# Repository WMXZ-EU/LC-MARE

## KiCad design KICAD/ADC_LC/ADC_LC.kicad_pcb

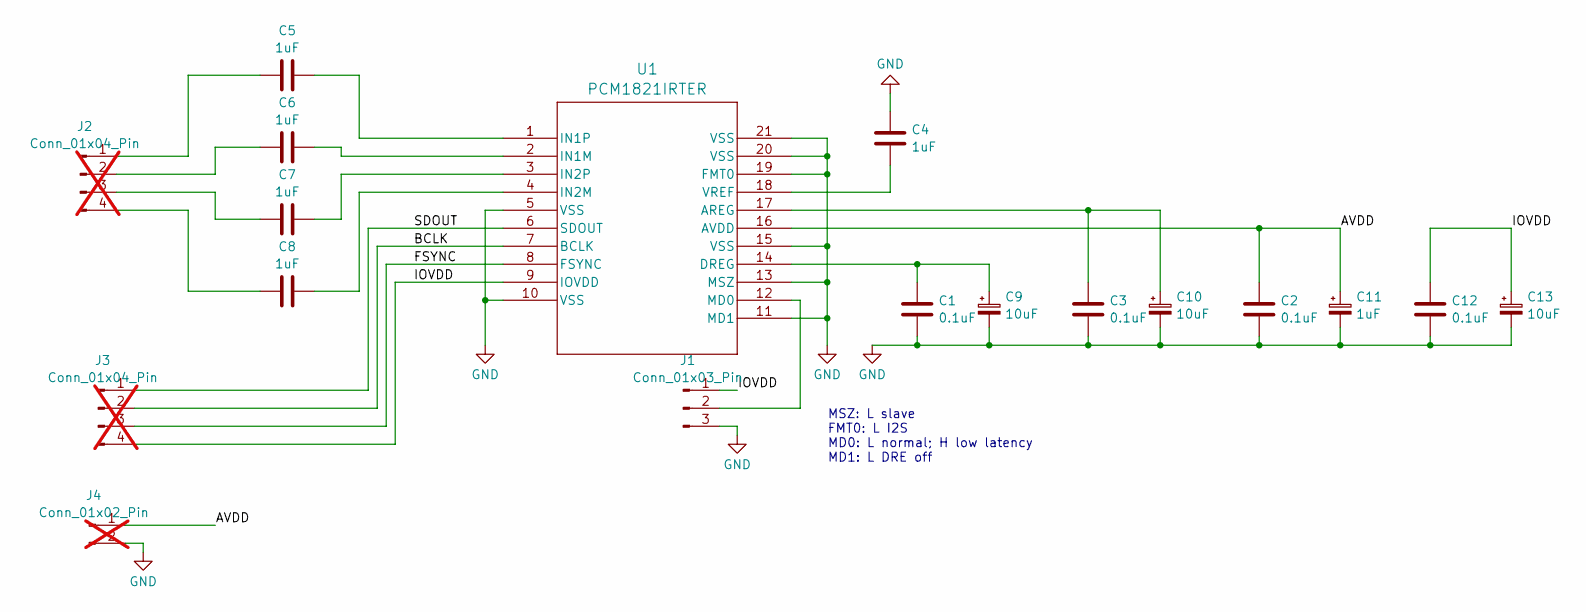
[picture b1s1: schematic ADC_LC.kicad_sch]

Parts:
C1, C2, C3, C12: 0.1uF; C_0402_1005Metric
C4, C5, C6, C7, C8: 1uF; C_0402_1005Metric
C9, C10, C13: 10uF; C_0805_2012Metric
C11: 1uF; C_0805_2012Metric
J1: Conn_01x03_Pin; SolderJumper-3_P1.3mm_Open_Pad1.0x1.5mm
J2, J3: Conn_01x04_Pin; PinHeader_1x04_P2.54mm_Vertical; not fitted
J4: Conn_01x02_Pin; PinHeader_1x02_P2.54mm_Vertical; not fitted
U1: PCM1821IRTER; QFN_820IRTER_TEX

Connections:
/AVDD: C2.1, C11.1, J4.1, U1.16 (AVDD)
/BCLK: J3.2, U1.7 (BCLK)
/FSYNC: J3.3, U1.8 (FSYNC)
/IOVDD: C12.1, C13.1, J1.1, J3.4, U1.9 (IOVDD)
/SDOUT: J3.1, U1.6 (SDOUT)
GND: C1.2, C2.2, C3.2, C4.1, C9.2, C10.2, C11.2, C12.2, C13.2, J1.3, J4.2, U1.5 (VSS), U1.10 (VSS), U1.11 (MD1), U1.13 (MSZ), U1.15 (VSS), U1.19 (FMT0), U1.20 (VSS), U1.21 (VSS)
unnamed: J1.2, U1.12 (MD0)
unnamed: C5.1, J2.1
unnamed: C6.1, J2.2
unnamed: C7.1, J2.3
unnamed: C8.1, J2.4
unnamed: C3.1, C10.1, U1.17 (AREG)
unnamed: C1.1, C9.1, U1.14 (DREG)
unnamed: C6.2, U1.2 (IN1M)
unnamed: C5.2, U1.1 (IN1P)
unnamed: C8.2, U1.4 (IN2M)
unnamed: C7.2, U1.3 (IN2P)
unnamed: C4.2, U1.18 (VREF)

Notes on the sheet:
MSZ: L slave FMT0: L I2S MD0: L normal; H low latency MD1: L DRE off

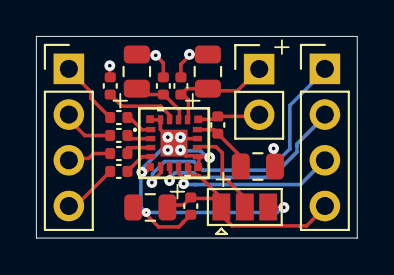
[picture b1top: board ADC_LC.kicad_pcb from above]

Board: 2 copper layers, 17.8 x 11.2 mm, 18 parts (0 on the bottom side), 18 nets.

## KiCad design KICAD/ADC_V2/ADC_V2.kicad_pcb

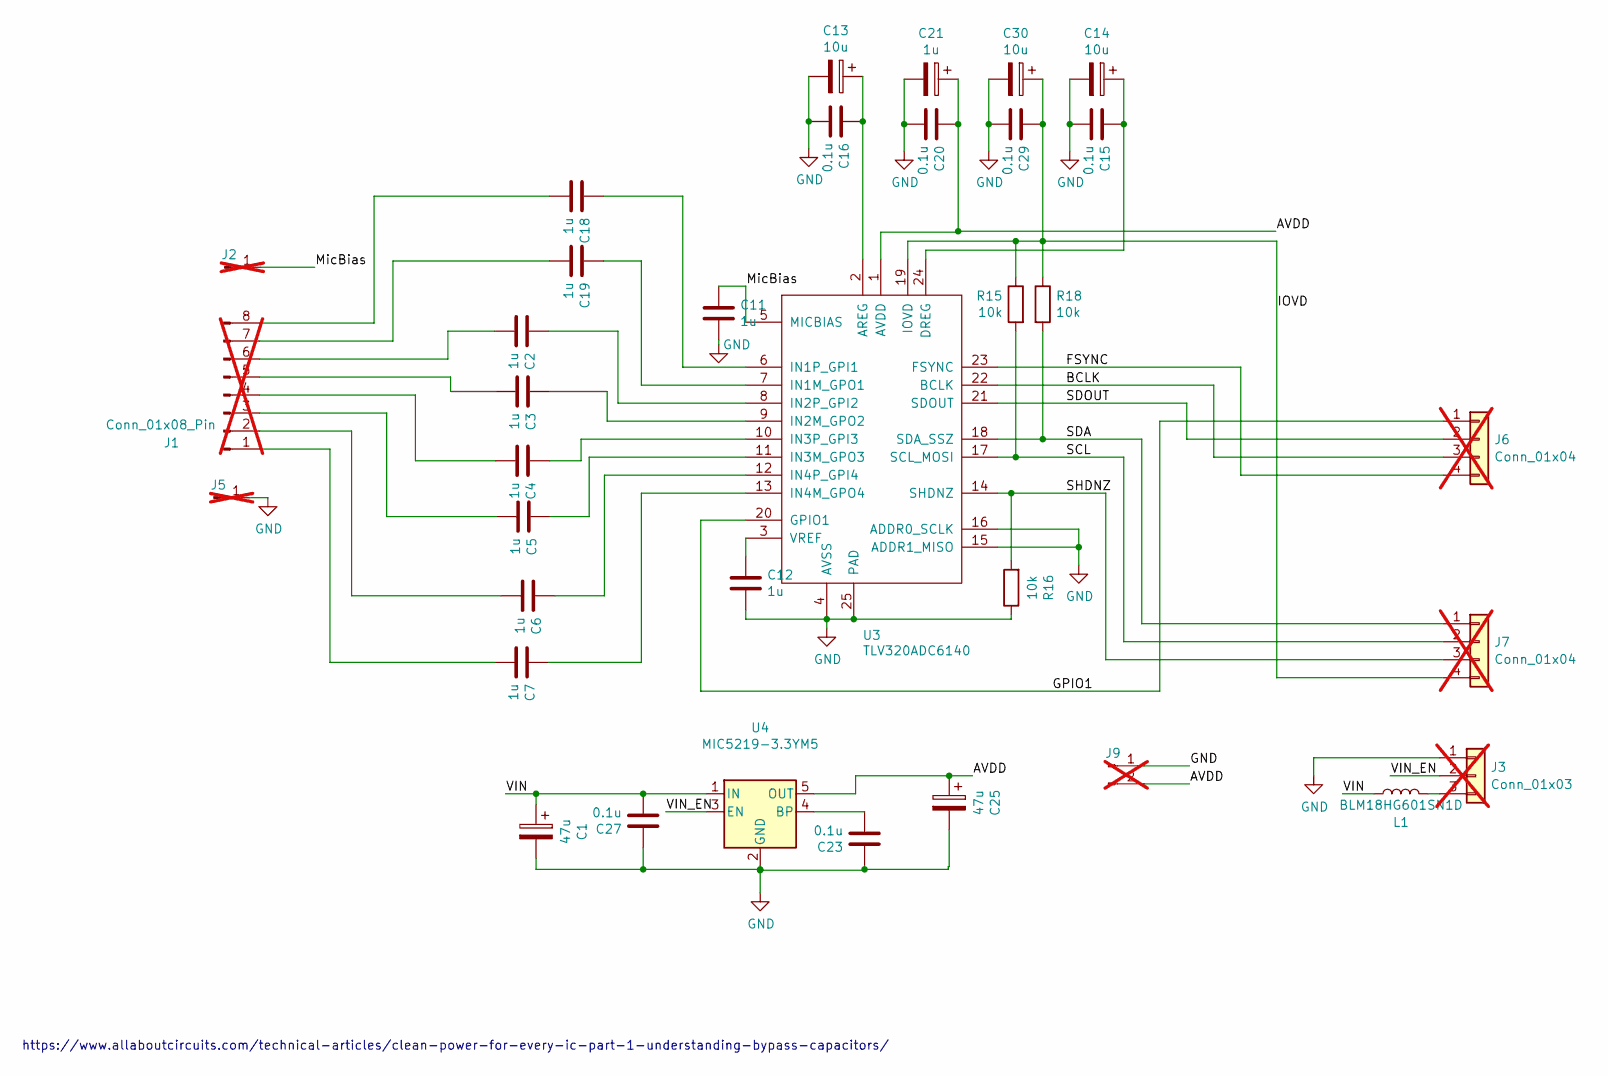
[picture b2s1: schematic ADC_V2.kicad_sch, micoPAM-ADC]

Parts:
C1, C25: 47u; CP_EIA-3216-12_Kemet-S
C2, C3, C4, C5, C6, C7, C11, C12, C18, C19: 1u; C_0603_1608Metric
C13, C14, C30: 10u; CP_EIA-2012-15_AVX-P
C15, C16, C20, C23, C27, C29: 0.1u; C_0603_1608Metric
C21: 1u; CP_EIA-2012-15_AVX-P
J1: Conn_01x08_Pin; PinHeader_1x08_P1.27mm_Vertical; not fitted
J2, J5: Conn_01x01_Pin; PinHeader_1x01_P2.54mm_Vertical; not fitted
J3: Conn_01x03; PinHeader_1x03_P1.27mm_Vertical; not fitted
J6, J7: Conn_01x04; PinHeader_1x04_P1.27mm_Vertical; not fitted
J9: Conn_01x02_Pin; PinHeader_1x02_P1.27mm_Vertical; not fitted
L1: BLM18HG601SN1D; L_0603_1608Metric
R15, R16, R18: 10k; R_0603_1608Metric
U3: TLV320ADC6140; QFN-24-1EP_4x4mm_P0.5mm_EP2.7x2.7mm_ThermalVias
U4: MIC5219-3.3YM5; SOT-23-5

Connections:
/AVDD: C20.1, C21.1, C25.1, J9.2, U3.1 (AVDD), U4.5 (OUT)
/BCLK: J6.3, U3.22 (BCLK)
/FSYNC: J6.4, U3.23 (FSYNC)
/GPIO1: J6.1, U3.20 (GPIO1)
/IOVD: C29.1, C30.1, J7.4, R15.1, R18.1, U3.19 (IOVD)
/MicBias: C11.1, J2.1, U3.5 (MICBIAS)
/SCL: J7.2, R15.2, U3.17 (SCL_MOSI)
/SDA: J7.1, R18.2, U3.18 (SDA_SSZ)
/SDOUT: J6.2, U3.21 (SDOUT)
/SHDNZ: J7.3, R16.2, U3.14 (SHDNZ)
/VIN: C1.1, C27.2, L1.1, U4.1 (IN)
/VIN_EN: J3.2, U4.3 (EN)
GND: C1.2, C11.2, C12.2, C13.2, C14.2, C15.2, C16.2, C20.2, C21.2, C23.1, C25.2, C27.1, C29.2, C30.2, J3.1, J5.1, J9.1, R16.1, U3.4 (AVSS), U3.15 (ADDR1_MISO), U3.16 (ADDR0_SCLK), U3.25 (PAD), U4.2 (GND)
unnamed: C7.2, J1.1
unnamed: C6.2, J1.2
unnamed: C5.2, J1.3
unnamed: C4.2, J1.4
unnamed: C3.2, J1.5
unnamed: C2.2, J1.6
unnamed: C19.2, J1.7
unnamed: C18.2, J1.8
unnamed: J3.3, L1.2
unnamed: C13.1, C16.1, U3.2 (AREG)
unnamed: C14.1, C15.1, U3.24 (DREG)
unnamed: C19.1, U3.7 (IN1M_GPO1)
unnamed: C18.1, U3.6 (IN1P_GPI1)
unnamed: C3.1, U3.9 (IN2M_GPO2)
unnamed: C2.1, U3.8 (IN2P_GPI2)
unnamed: C5.1, U3.11 (IN3M_GPO3)
unnamed: C4.1, U3.10 (IN3P_GPI3)
unnamed: C7.1, U3.13 (IN4M_GPO4)
unnamed: C6.1, U3.12 (IN4P_GPI4)
unnamed: C12.1, U3.3 (VREF)
unnamed: C23.2, U4.4 (BP)

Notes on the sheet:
https://www.allaboutcircuits.com/technical-articles/clean-power-for-every-ic-part-1-understanding-bypass-capacitors/

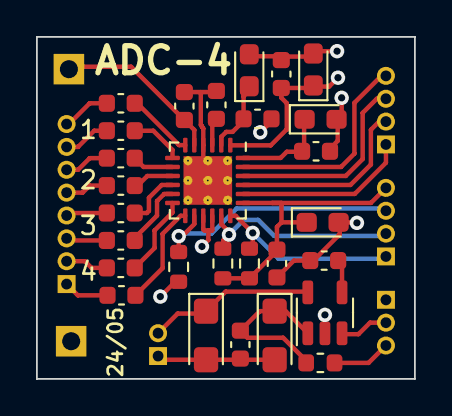
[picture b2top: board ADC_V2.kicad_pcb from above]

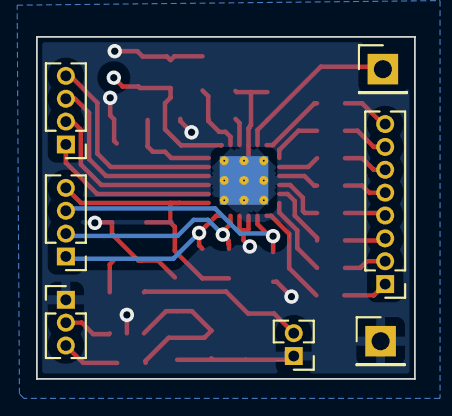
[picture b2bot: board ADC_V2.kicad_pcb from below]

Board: 4 copper layers, 21.0 x 19.0 mm, 35 parts (7 on the bottom side), 34 nets.

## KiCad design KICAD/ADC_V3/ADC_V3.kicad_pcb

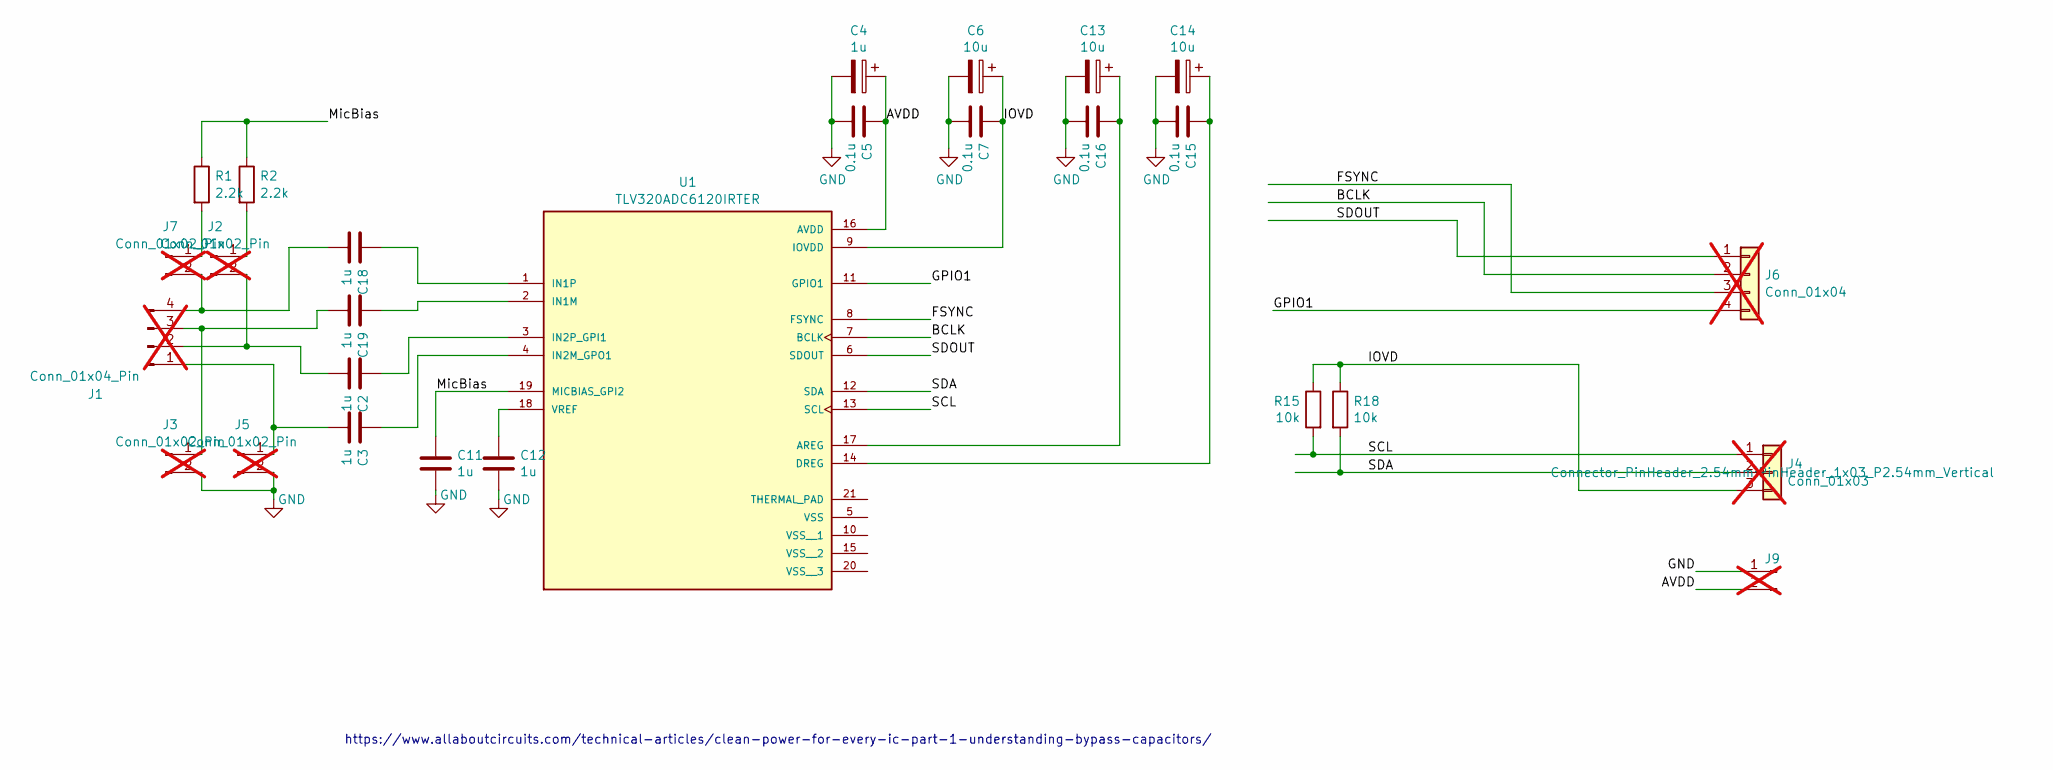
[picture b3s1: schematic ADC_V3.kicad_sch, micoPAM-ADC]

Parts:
C2, C3, C11, C12, C18, C19: 1u; C_0603_1608Metric
C4: 1u; CP_EIA-2012-15_AVX-P
C5, C7, C15, C16: 0.1u; C_0603_1608Metric
C6, C13, C14: 10u; CP_EIA-2012-15_AVX-P
J1: Conn_01x04_Pin; PinHeader_1x04_P2.54mm_Vertical; not fitted
J2, J3, J5, J7: Conn_01x02_Pin; PinHeader_1x02_P1.00mm_Vertical; not fitted
J4: Conn_01x03; PinHeader_1x03_P2.54mm_Vertical; not fitted
J6: Conn_01x04; PinHeader_1x04_P2.54mm_Vertical; not fitted
J9: Conn_01x02_Pin; PinHeader_1x02_P2.54mm_Vertical; not fitted
R1, R2: 2.2k; R_0402_1005Metric
R15, R18: 10k; R_0603_1608Metric
U1: TLV320ADC6120IRTER; IC_TLV320ADC6120IRTER; PARTREV A

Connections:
/AVDD: C4.1, C5.1, J9.2, U1.16 (AVDD)
/BCLK: J6.2, U1.7 (BCLK)
/FSYNC: J6.3, U1.8 (FSYNC)
/GPIO1: J6.4, U1.11 (GPIO1)
/IOVD: C6.1, C7.1, J4.3, R15.1, R18.1, U1.9 (IOVDD)
/MicBias: C11.1, R1.1, R2.1, U1.19 (MICBIAS_GPI2)
/SCL: J4.1, R15.2, U1.13 (SCL)
/SDA: J4.2, R18.2, U1.12 (SDA)
/SDOUT: J6.1, U1.6 (SDOUT)
GND: C4.2, C5.2, C6.2, C7.2, C11.2, C12.2, C13.2, C14.2, C15.2, C16.2, J3.2, J5.2, J9.1, U1.5 (VSS), U1.10 (VSS__1), U1.15 (VSS__2), U1.20 (VSS__3), U1.21 (THERMAL_PAD), U1.22, U1.23, U1.24, U1.25
unnamed: C3.2, J1.1, J5.1
unnamed: C2.2, J1.2, J2.2
unnamed: C19.2, J1.3, J3.1
unnamed: C18.2, J1.4, J7.2
unnamed: J2.1, R2.2
unnamed: J7.1, R1.2
unnamed: C13.1, C16.1, U1.17 (AREG)
unnamed: C14.1, C15.1, U1.14 (DREG)
unnamed: C19.1, U1.2 (IN1M)
unnamed: C18.1, U1.1 (IN1P)
unnamed: C3.1, U1.4 (IN2M_GPO1)
unnamed: C2.1, U1.3 (IN2P_GPI1)
unnamed: C12.1, U1.18 (VREF)

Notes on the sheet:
https://www.allaboutcircuits.com/technical-articles/clean-power-for-every-ic-part-1-understanding-bypass-capacitors/

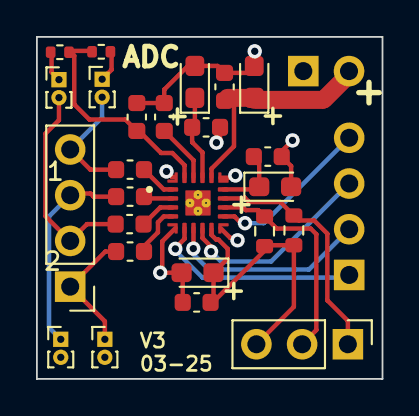
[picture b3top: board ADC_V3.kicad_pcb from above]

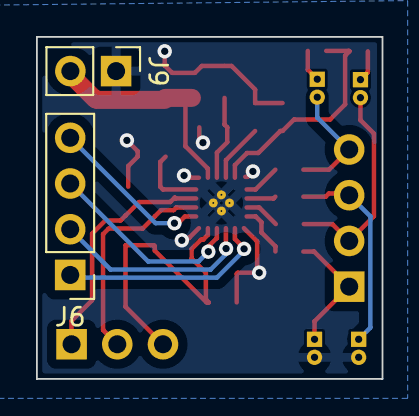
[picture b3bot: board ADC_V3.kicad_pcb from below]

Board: 2 copper layers, 19.2 x 19.0 mm, 27 parts (2 on the bottom side), 23 nets.

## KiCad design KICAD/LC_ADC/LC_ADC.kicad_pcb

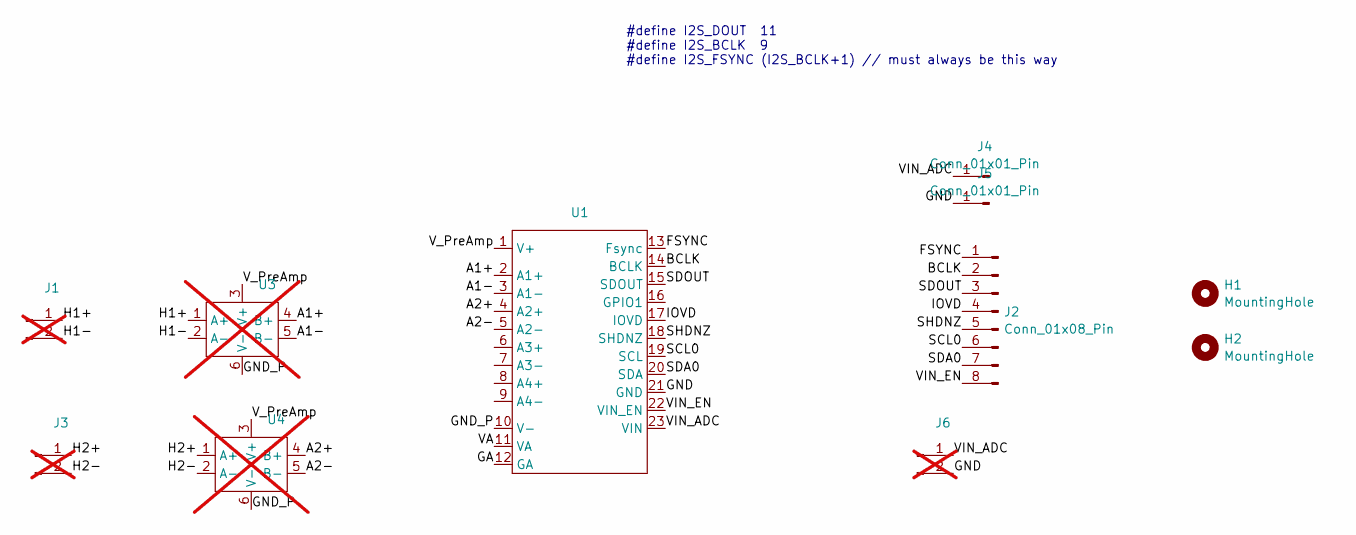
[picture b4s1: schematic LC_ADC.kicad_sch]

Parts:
H1, H2: MountingHole; MountingHole_3.2mm_M3
J1, J3: Conn_01x02_Male; Molex_PicoBlade_53048-0210_1x02_P1.25mm_Horizontal; not fitted
J2: Conn_01x08_Pin; PinHeader_1x08_P2.54mm_Vertical
J4, J5: Conn_01x01_Pin; PinHeader_1x01_P2.54mm_Vertical
J6: Conn_01x02_Male; PinHeader_1x02_P1.27mm_Vertical; not fitted
U1: ADC_V2
U3, U4: preAmp2; not fitted

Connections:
/A1+: U1.2 (A1+), U3.4 (B+)
/A1-: U1.3 (A1-), U3.5 (B-)
/A2+: U1.4 (A2+), U4.4 (B+)
/A2-: U1.5 (A2-), U4.5 (B-)
/BCLK: J2.2, U1.14 (BCLK)
/FSYNC: J2.1, U1.13 (Fsync)
/GA: U1.12 (GA)
/GND: J5.1, J6.2, U1.21 (GND)
/GND_P: U1.10 (V-), U3.6 (V-), U4.6 (V-)
/H1+: J1.1, U3.1 (A+)
/H1-: J1.2, U3.2 (A-)
/H2+: J3.1, U4.1 (A+)
/H2-: J3.2, U4.2 (A-)
/IOVD: J2.4, U1.17 (IOVD)
/SCL0: J2.6, U1.19 (SCL)
/SDA0: J2.7, U1.20 (SDA)
/SDOUT: J2.3, U1.15 (SDOUT)
/SHDNZ: J2.5, U1.18 (SHDNZ)
/VA: U1.11 (VA)
/VIN_ADC: J4.1, J6.1, U1.23 (VIN)
/VIN_EN: J2.8, U1.22 (VIN_EN)
/V_PreAmp: U1.1 (V+), U3.3 (V+), U4.3 (V+)

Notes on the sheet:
#define I2S_DOUT 11 #define I2S_BCLK 9 #define I2S_FSYNC (I2S_BCLK+1) // must always be this way

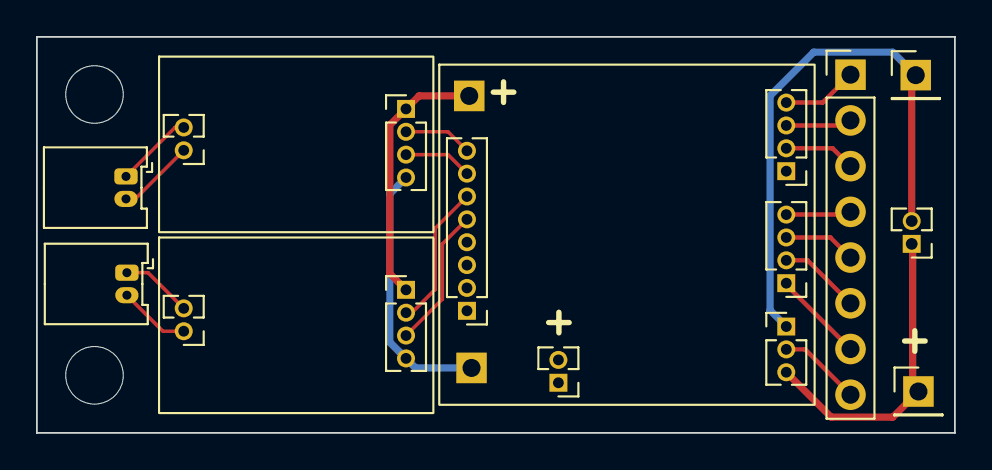
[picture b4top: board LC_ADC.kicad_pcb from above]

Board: 2 copper layers, 51.0 x 22.0 mm, 12 parts (0 on the bottom side), 20 nets.

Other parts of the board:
J10: rtc; rtc2

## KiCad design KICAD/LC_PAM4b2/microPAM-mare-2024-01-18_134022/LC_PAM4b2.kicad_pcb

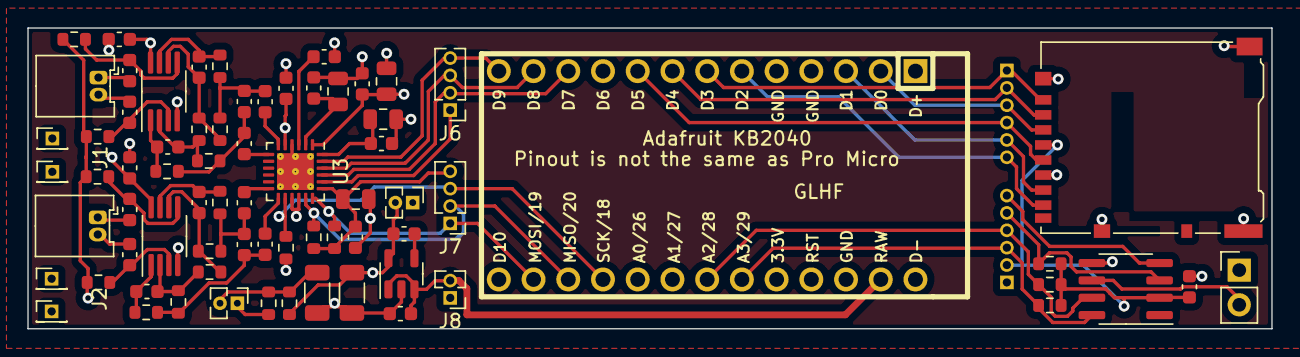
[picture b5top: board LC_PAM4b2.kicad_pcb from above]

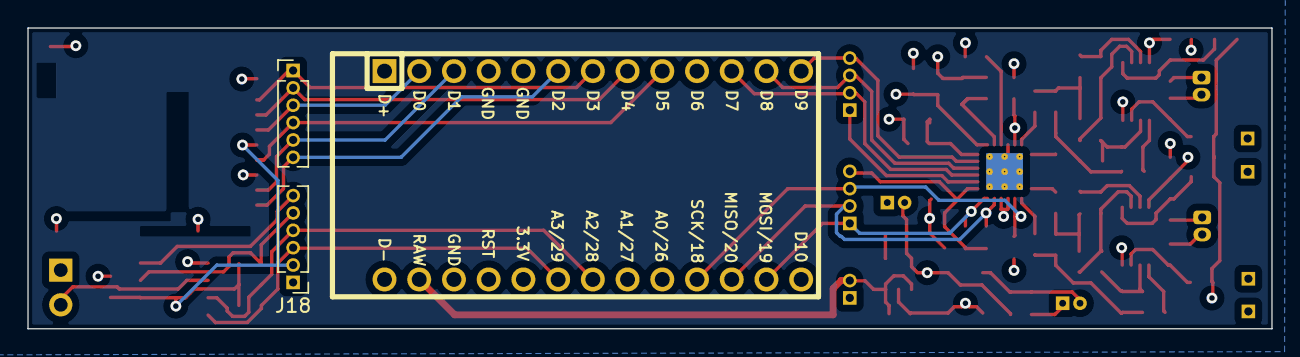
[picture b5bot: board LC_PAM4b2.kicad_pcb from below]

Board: 4 copper layers, 91.0 x 22.0 mm, 74 parts (2 on the bottom side), 52 nets.

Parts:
C1, C2, C7, C8, C11, C12, C18, C19, C24, C28: 1u; C_0603_1608Metric
C3, C4, C9, C10: 15p; C_0603_1608Metric
C5, C6, C15, C16, C20, C23, C27, C29, C101: 0.1u; C_0603_1608Metric
C13, C14, C30: 10u; C_0805_2012Metric
C17, C22: 2700p; C_0603_1608Metric
C21: 1u; C_0805_2012Metric
C25, C26: 47u; C_1206_3216Metric
J1, J2: Conn_01x02_Male; Molex_PicoBlade_53048-0210_1x02_P1.25mm_Horizontal
J3, J4, J5, J11: Conn_01x01_Pin; PinHeader_1x01_P1.27mm_Vertical
J6, J7: Conn_01x04; PinHeader_1x04_P1.27mm_Vertical
J8: Conn_01x02; PinHeader_1x02_P1.27mm_Vertical
J9, J10: Conn_01x02_Pin; PinHeader_1x02_P1.27mm_Vertical
J14, J18: Conn_01x06_Pin; PinHeader_1x06_P1.27mm_Vertical
J15: Conn_01x02_Pin; PinHeader_1x02_P2.54mm_Vertical
J16: Micro_SD_Card_Det_Hirose_DM3AT; microSD_HC_Hirose_DM3AT-SF-PEJM5
R1, R7, R8, R14, R16: 10k; R_0603_1608Metric
R2, R3, R9, R10: 2M; R_0603_1608Metric
R4, R11: 1k; R_0603_1608Metric
R5, R6, R12, R13: 49R; R_0603_1608Metric
R15, R18, R101, R102, R103: 4.7k; R_0603_1608Metric
R17, R19: 100k; R_0603_1608Metric
U1, U2: AD8656; MSOP-8_3x3mm_P0.65mm
U3: TLV320ADC6140; QFN-24-1EP_4x4mm_P0.5mm_EP2.7x2.7mm_ThermalVias
U4: MIC5219-3.3YM5; SOT-23-5
U51: kb2040
U102: DS3232M; SOIC-8_3.9x4.9mm_P1.27mm

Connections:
/AVDD: C5.1, C6.1, C20.1, C21.1, C23.2, C25.1, J9.2, R17.1, U1.8 (V+), U2.8 (V+), U3.1 (AVDD), U4.5 (OUT)
/BCLK: J6.3, U3.22 (BCLK), U51.12 (D8)
/CMD: J14.3, J16.3 (CMD), U51.2 (D0)
/DAT0: J14.5, J16.7 (DAT0), U51.3 (D1)
/DAT1: J14.6, J16.8 (DAT1), U51.6 (D2)
/DAT2: J14.1, J16.1 (DAT2), U51.7 (D3)
/DAT3: J14.2, J16.2 (DAT3/CD), U51.8 (D4)
/DIn: J6.2, U3.21 (SDOUT), U51.11 (D7)
/FSYNC: J6.4, U3.23 (FSYNC), U51.13 (D9)
/GPIO1: J6.1, U3.20 (GPIO1)
/MicBias: C11.1, J3.1, J4.1, U3.5 (MICBIAS)
/SCK: J14.4, J16.5 (CLK), U51.9 (D5)
/SCL1: J7.2, R15.2, U3.17 (SCL_MOSI), U51.24 (MISO/20)
/SDA1: J7.1, R18.2, U3.18 (SDA_SSZ), U51.25 (MOSI/19)
/SHDNZ: J7.3, R16.2, U3.14 (SHDNZ), U51.23 (SCK/18)
/VCOM: C26.1, J10.2, R2.2, R3.1, R9.2, R10.1, R17.2, R19.1
/VIN: C27.2, J8.2, U4.1 (IN), U4.3 (EN), U51.15 (RAW)
/nRST: J18.6, U102.4 (~RST)
GND: C5.2, C6.2, C11.2, C12.2, C13.2, C14.2, C15.2, C16.2, C20.2, C21.2, C25.2, C26.2, C27.1, C29.2, C30.2, C101.2, J5.1, J8.1, J9.1, J10.1, J11.1, J15.1, J16.6 (VSS), J16.11 (SHIELD), J18.1, R16.1, R19.2, U1.4 (V-), U2.4 (V-), U3.4 (AVSS), U3.15 (ADDR1_MISO), U3.16 (ADDR0_SCLK), U3.25 (PAD), U4.2 (GND), U51.4 (GND), U51.5 (GND), U51.16 (GND), U102.5 (GND)
IOVD: C29.1, C30.1, C101.1, J7.4, J16.4 (VDD), J18.2, R15.1, R18.1, R101.1, R102.1, R103.1, U3.19 (IOVD), U51.18 (3.3v), U102.2 (VCC)
unnamed: C3.2, R5.2, U1.1
unnamed: C4.1, R6.2, U1.7
unnamed: C9.2, R12.2, U2.1
unnamed: C10.1, R13.2, U2.7
unnamed: C17.1, C19.2, R1.1, R5.1
unnamed: C17.2, C18.2, R6.1, R7.1
unnamed: C22.1, C28.2, R8.1, R12.1
unnamed: C22.2, C24.2, R13.1, R14.1
unnamed: C2.2, J1.1
unnamed: C1.2, J1.2
unnamed: C8.2, J2.1
unnamed: C7.2, J2.2
unnamed: C1.1, R2.1, U1.3 (+)
unnamed: C3.1, R1.2, R4.1, U1.2 (-)
unnamed: C2.1, R3.2, U1.5 (+)
unnamed: C4.2, R4.2, R7.2, U1.6 (-)
unnamed: C7.1, R9.1, U2.3 (+)
unnamed: C9.1, R8.2, R11.1, U2.2 (-)
unnamed: C8.1, R10.2, U2.5 (+)
unnamed: C10.2, R11.2, R14.2, U2.6 (-)
unnamed: C13.1, C16.1, U3.2 (AREG)
unnamed: C14.1, C15.1, U3.24 (DREG)
unnamed: C19.1, U3.7 (IN1M_GPO1)
unnamed: C18.1, U3.6 (IN1P_GPI1)
unnamed: C28.1, U3.13 (IN4M_GPO4)
unnamed: C24.1, U3.12 (IN4P_GPI4)
unnamed: C12.1, U3.3 (VREF)
unnamed: C23.1, U4.4 (BP)
SCL0: J18.3, R101.2, U51.19 (A3/29), U102.8 (SCL)
SDA0: J18.4, R102.2, U51.20 (A2/28), U102.7 (SDA)
VBAT: J15.2, U102.6 (VBAT)
nINT: J18.5, R103.2, U102.3 (~INT/SQW)

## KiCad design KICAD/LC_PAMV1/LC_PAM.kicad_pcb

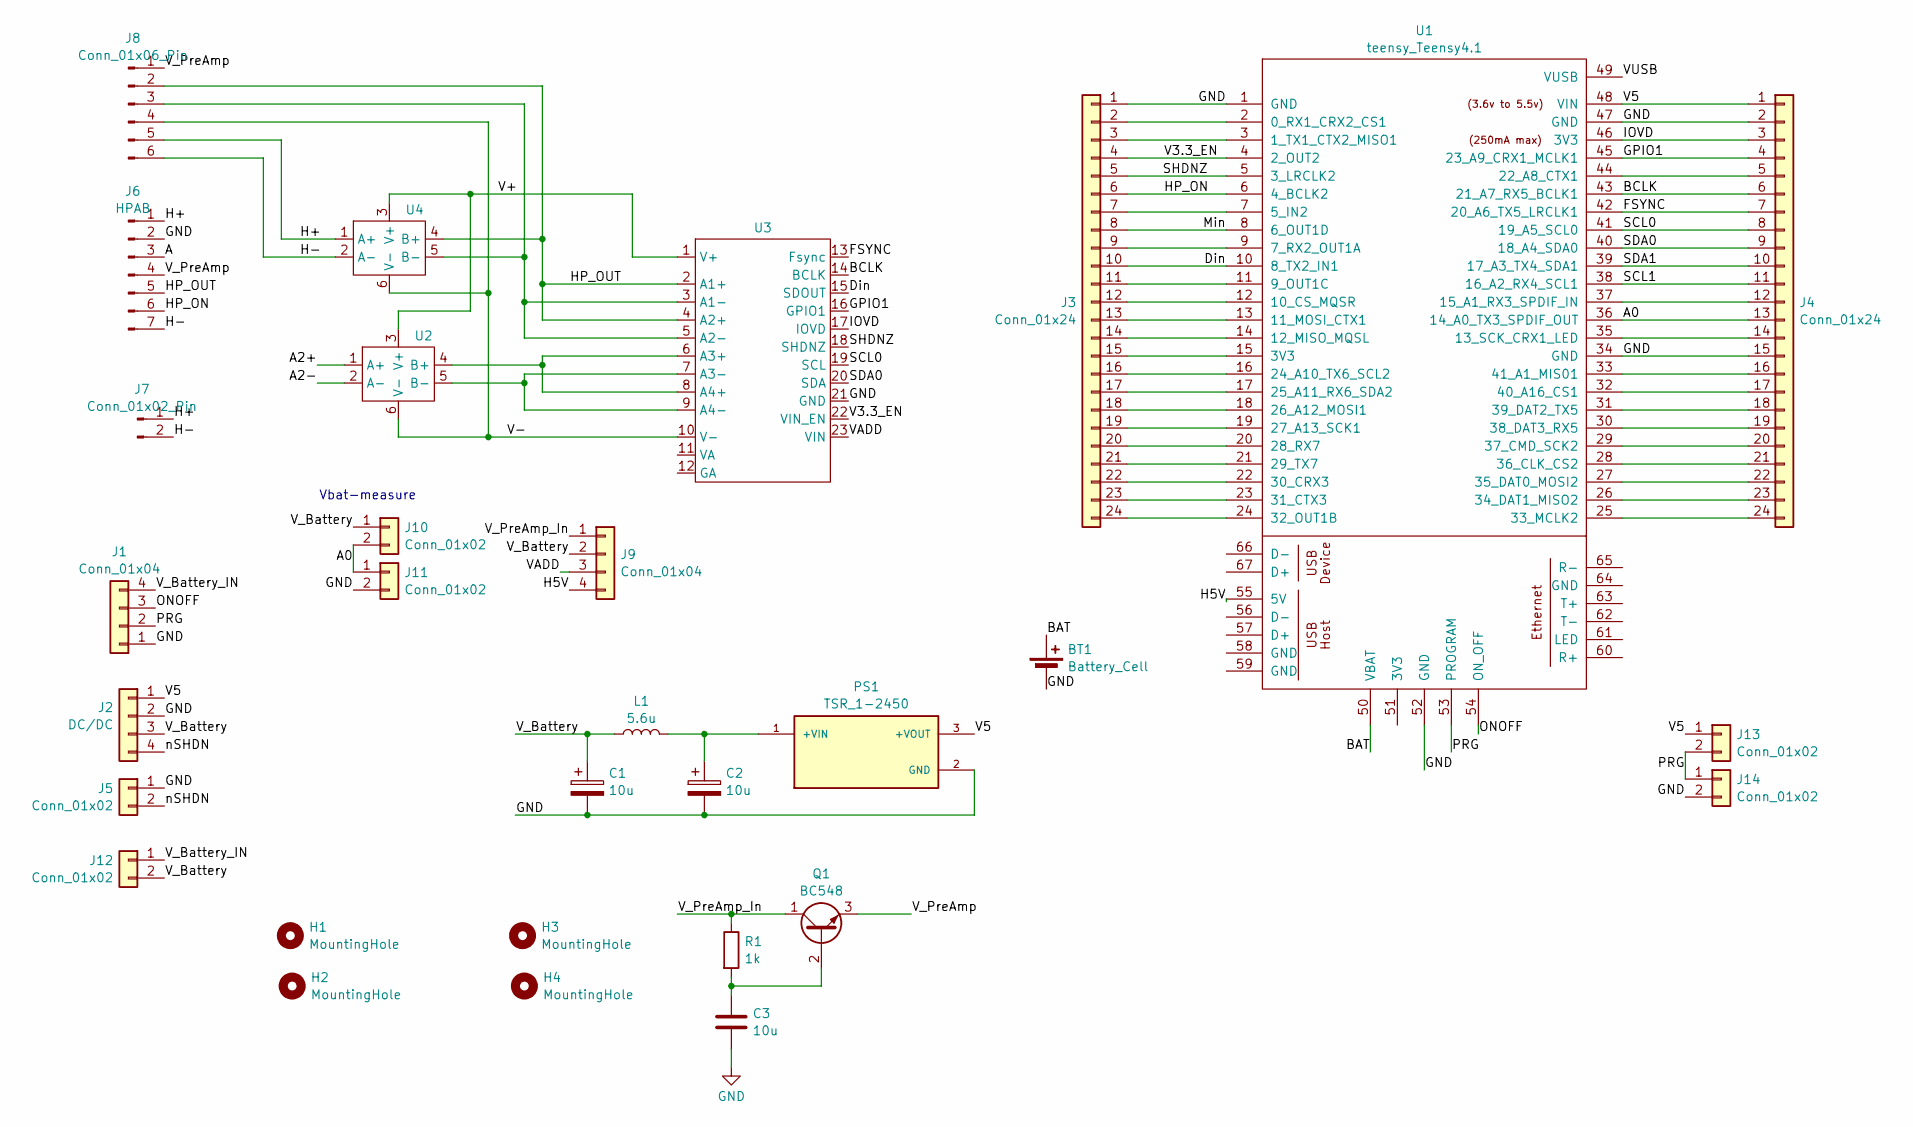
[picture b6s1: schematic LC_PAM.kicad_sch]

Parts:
BT1: Battery_Cell; PinHeader_1x02_P2.54mm_Vertical
C1, C2: 10u; CP_Radial_D6.3mm_P2.50mm
C3: 10u; CP_Radial_D4.0mm_P1.50mm
H1, H2, H3, H4: MountingHole; MountingHole_3.2mm_M3
J1: Conn_01x04; PinHeader_1x04_P2.54mm_Vertical
J2: DC/DC; PinHeader_1x04_P2.54mm_Vertical
J3, J4: Conn_01x24; PinHeader_1x24_P2.54mm_Vertical
J5, J12: Conn_01x02; PinHeader_1x02_P2.54mm_Vertical
J6: HPAB
J7: Conn_01x02_Pin; Molex_PicoBlade_53047-0210_1x02_P1.25mm_Vertical
J8: Conn_01x06_Pin; Preamp-FET
J9: Conn_01x04; SolderWire-0.1sqmm_1x04_P3.6mm_D0.4mm_OD1mm
J10, J11, J13, J14: Conn_01x02; R_Axial_DIN0204_L3.6mm_D1.6mm_P1.90mm_Vertical
L1: 5.6u; L_Axial_L11.0mm_D4.5mm_P15.24mm_Horizontal_Fastron_MECC
PS1: TSR_1-2450; Converter_DCDC_TRACO_TSR-1_THT; PARTREV Apr 27, 2020
Q1: BC548; TO-92_Inline
R1: 1k; R_Axial_DIN0204_L3.6mm_D1.6mm_P2.54mm_Vertical
U1: teensy_Teensy4.1; Teensy41
U2, U4: preAmp2
U3: ADC_V2

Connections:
/A: J6.3
/A0: J4.13, J10.2, J11.1, U1.36 (14_A0_TX3_SPDIF_OUT)
/A2+: U2.1 (A+)
/A2-: U2.2 (A-)
/BAT: BT1.1 (+), U1.50 (VBAT)
/BCLK: J4.6, U1.43 (21_A7_RX5_BCLK1), U3.14 (BCLK)
/Din: J3.10, U1.10 (8_TX2_IN1), U3.15 (SDOUT)
/FSYNC: J4.7, U1.42 (20_A6_TX5_LRCLK1), U3.13 (Fsync)
/GPIO1: J4.4, U1.45 (23_A9_CRX1_MCLK1), U3.16 (GPIO1)
/H5V: J9.4, U1.55 (5V)
/H+: J6.1, J7.1, J8.5, U4.1 (A+)
/H-: J6.7, J7.2, J8.6, U4.2 (A-)
/HP_ON: J3.6, J6.6, U1.6 (4_BCLK2)
/HP_OUT: J6.5, J8.2, U3.2 (A1+), U3.4 (A2+), U4.4 (B+)
/IOVD: J4.3, U1.46 (3V3), U3.17 (IOVD)
/Min: J3.8, U1.8 (6_OUT1D)
/ONOFF: J1.3, U1.54 (ON_OFF)
/PRG: J1.2, J13.2, J14.1, U1.53 (PROGRAM)
/SCL0: J4.8, U1.41 (19_A5_SCL0), U3.19 (SCL)
/SCL1: J4.11, U1.38 (16_A2_RX4_SCL1)
/SDA0: J4.9, U1.40 (18_A4_SDA0), U3.20 (SDA)
/SDA1: J4.10, U1.39 (17_A3_TX4_SDA1)
/SHDNZ: J3.5, U1.5 (3_LRCLK2), U3.18 (SHDNZ)
/V3.3_EN: J3.4, U1.4 (2_OUT2), U3.22 (VIN_EN)
/V5: J2.1, J4.1, J13.1, PS1.3 (+VOUT), U1.48 (VIN)
/V+: U2.3 (V+), U3.1 (V+), U4.3 (V+)
/V-: J8.4, U2.6 (V-), U3.10 (V-), U4.6 (V-)
/VADD: J9.3, U3.23 (VIN)
/VUSB: U1.49 (VUSB)
/V_Battery: C1.1, J2.3, J9.2, J10.1, J12.2, L1.1
/V_Battery_IN: J1.4, J12.1
/V_PreAmp: J6.4, J8.1, Q1.3 (E)
/V_PreAmp_In: J9.1, Q1.1 (C), R1.1
/nSHDN: J2.4, J5.2
GND: BT1.2 (-), C1.2, C2.2, C3.2, J1.1, J2.2, J3.1, J4.2, J4.15, J5.1, J6.2, J11.2, J14.2, PS1.2 (GND), U1.1 (GND), U1.34 (GND), U1.47 (GND), U1.52 (GND), U3.21 (GND)
unnamed: J3.2, U1.2 (0_RX1_CRX2_CS1)
unnamed: J3.3, U1.3 (1_TX1_CTX2_MISO1)
unnamed: J3.7, U1.7 (5_IN2)
unnamed: J3.9, U1.9 (7_RX2_OUT1A)
unnamed: J3.11, U1.11 (9_OUT1C)
unnamed: J3.12, U1.12 (10_CS_MQSR)
unnamed: J3.13, U1.13 (11_MOSI_CTX1)
unnamed: J3.14, U1.14 (12_MISO_MQSL)
unnamed: J3.15, U1.15 (3V3)
unnamed: J3.16, U1.16 (24_A10_TX6_SCL2)
unnamed: J3.17, U1.17 (25_A11_RX6_SDA2)
unnamed: J3.18, U1.18 (26_A12_MOSI1)
unnamed: J3.19, U1.19 (27_A13_SCK1)
unnamed: J3.20, U1.20 (28_RX7)
unnamed: J3.21, U1.21 (29_TX7)
unnamed: J3.22, U1.22 (30_CRX3)
unnamed: J3.23, U1.23 (31_CTX3)
unnamed: J3.24, U1.24 (32_OUT1B)
unnamed: J4.5, U1.44 (22_A8_CTX1)
unnamed: J4.12, U1.37 (15_A1_RX3_SPDIF_IN)
unnamed: J4.14, U1.35 (13_SCK_CRX1_LED)
unnamed: J4.16, U1.33 (41_A1_MIS01)
unnamed: J4.17, U1.32 (40_A16_CS1)
unnamed: J4.18, U1.31 (39_DAT2_TX5)
unnamed: J4.19, U1.30 (38_DAT3_RX5)
unnamed: J4.20, U1.29 (37_CMD_SCK2)
unnamed: J4.21, U1.28 (36_CLK_CS2)
unnamed: J4.22, U1.27 (35_DAT0_MOSI2)
unnamed: J4.23, U1.26 (34_DAT1_MISO2)
unnamed: J4.24, U1.25 (33_MCLK2)
unnamed: J8.3, U3.3 (A1-), U3.5 (A2-), U4.5 (B-)
unnamed: C2.1, L1.2, PS1.1 (+VIN)
unnamed: C3.1, Q1.2 (B), R1.2
unnamed: U2.4 (B+), U3.6 (A3+), U3.8 (A4+)
unnamed: U2.5 (B-), U3.7 (A3-), U3.9 (A4-)

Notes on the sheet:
Vbat-measure

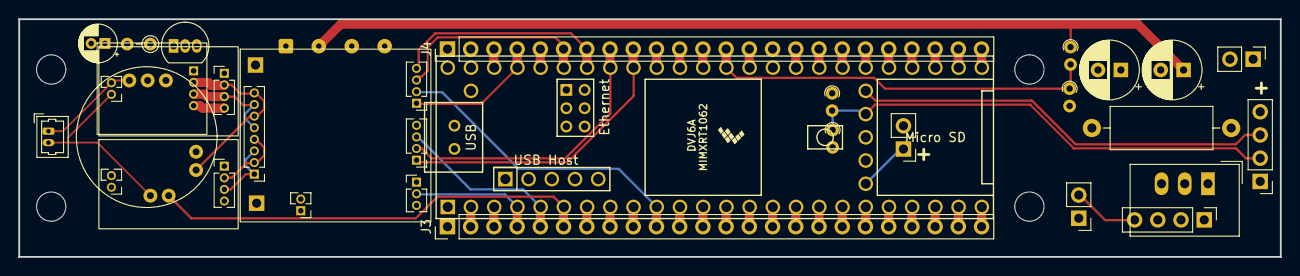
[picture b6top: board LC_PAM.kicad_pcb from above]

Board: 4 copper layers, 138.0 x 26.0 mm, 30 parts (0 on the bottom side), 66 nets.

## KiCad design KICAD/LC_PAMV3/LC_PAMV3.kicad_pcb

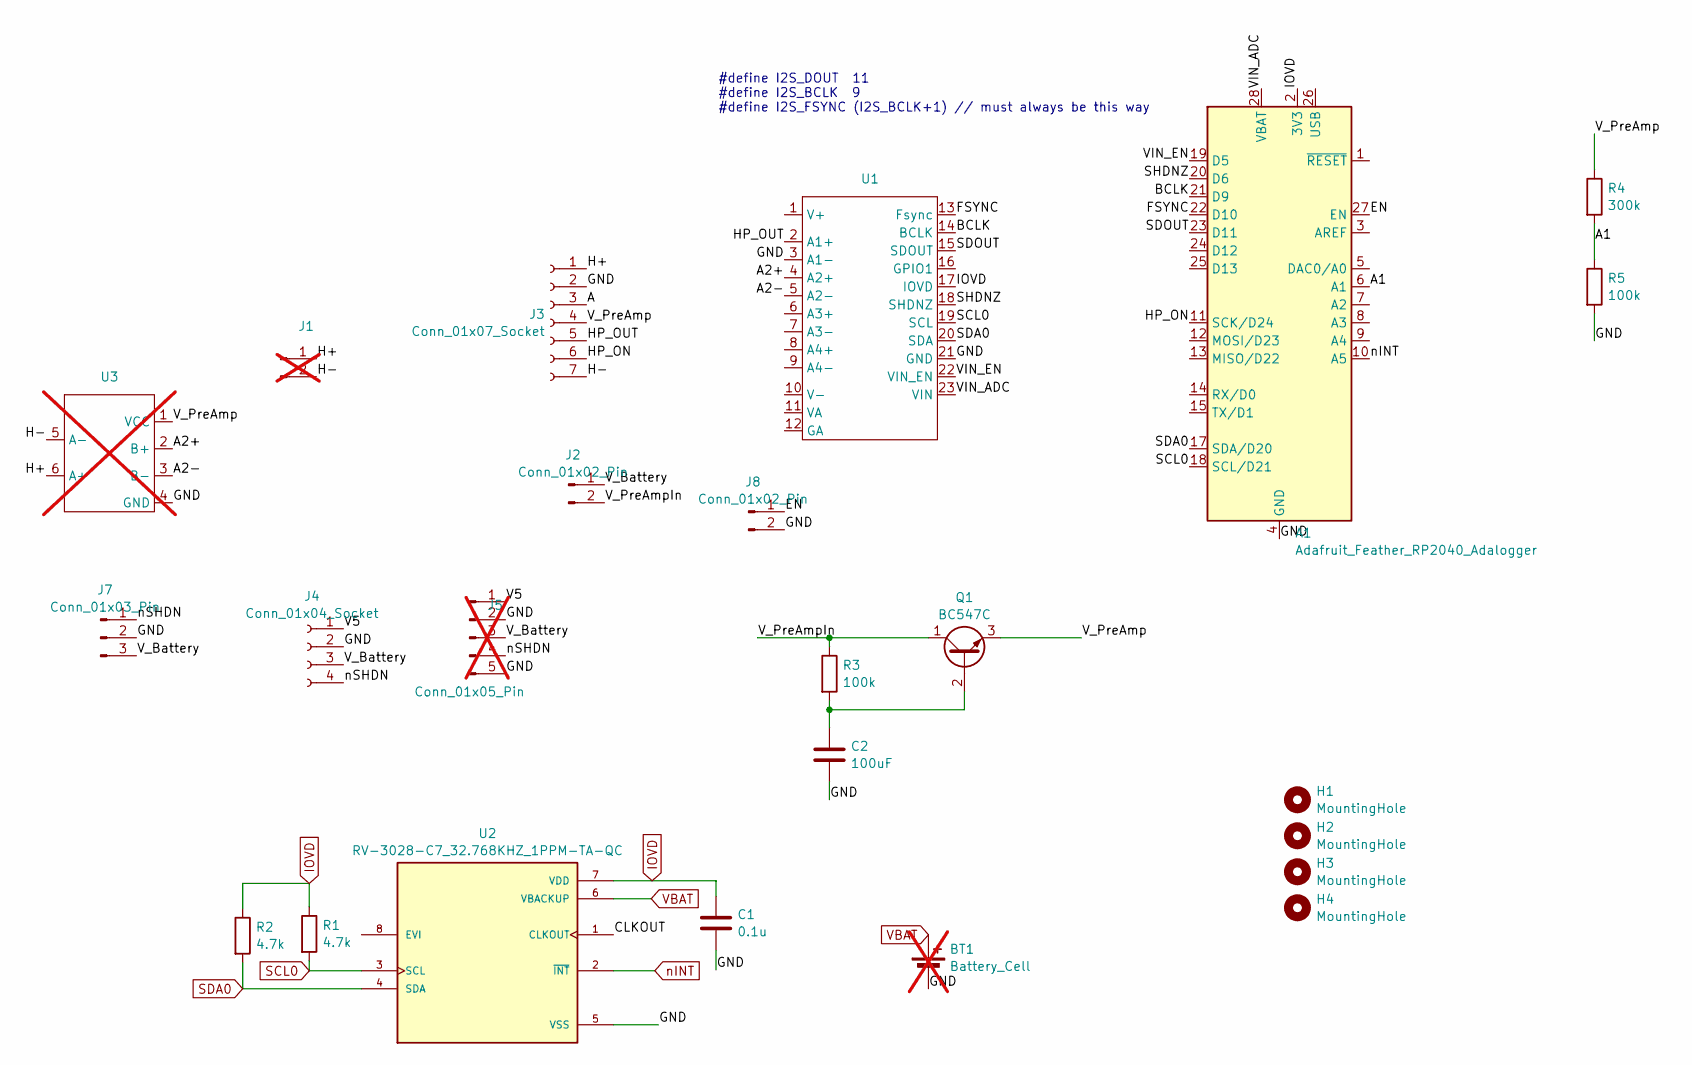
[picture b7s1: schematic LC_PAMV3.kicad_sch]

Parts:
A1: Adafruit_Feather_RP2040_Adalogger; Adafruit_Feather_WithMountingHoles
BT1: Battery_Cell; Supercap; not fitted
C1: 0.1u; C_0603_1608Metric
C2: 100uF; CP_Radial_D4.0mm_P2.00mm
H1, H2, H3, H4: MountingHole; MountingHole_3.2mm_M3_DIN965
J1: Conn_01x02_Male; Molex_PicoBlade_53048-0210_1x02_P1.25mm_Horizontal; not fitted
J2, J8: Conn_01x02_Pin; PinHeader_1x02_P2.54mm_Vertical
J3: Conn_01x07_Socket; HPAB
J4: Conn_01x04_Socket; PinHeader_1x04_P2.54mm_Vertical
J5: Conn_01x05_Pin; PinHeader_1x05_P2.54mm_Vertical; not fitted
J7: Conn_01x03_Pin; PinHeader_1x03_P2.54mm_Vertical
Q1: BC547C; TO-92_Inline
R1, R2: 4.7k; R_0603_1608Metric
R3, R5: 100k; R_Axial_DIN0204_L3.6mm_D1.6mm_P1.90mm_Vertical
R4: 300k; R_Axial_DIN0204_L3.6mm_D1.6mm_P1.90mm_Vertical
U1: ADC_V2
U2: RV-3028-C7_32.768KHZ_1PPM-TA-QC; IC_RV-3028-C7_32.768KHZ_1PPM-TA-QC; PARTREV 1.3
U3: Preamp-FET; not fitted

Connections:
/A: J3.3
/A1: A1.6 (A1), R4.2, R5.1
/A2+: U1.4 (A2+), U3.2 (B+)
/A2-: U1.5 (A2-), U3.3 (B-)
/BCLK: A1.21 (D9), U1.14 (BCLK)
/CLKOUT: U2.1 (CLKOUT)
/EN: A1.27 (EN), J8.1
/FSYNC: A1.22 (D10), U1.13 (Fsync)
/GND: A1.4 (GND), A1.16 (GND), BT1.2 (-), C1.2, C2.2, J3.2, J4.2, J5.2, J5.5, J7.2, J8.2, R5.2, U1.3 (A1-), U1.21 (GND), U2.5 (VSS), U3.4 (GND)
/H+: J1.1, J3.1, U3.6 (A+)
/H-: J1.2, J3.7, U3.5 (A-)
/HP_ON: A1.11 (SCK/D24), J3.6
/HP_OUT: J3.5, U1.2 (A1+)
/SDOUT: A1.23 (D11), U1.15 (SDOUT)
/SHDNZ: A1.20 (D6), U1.18 (SHDNZ)
/V5: J4.1, J5.1
/VIN_ADC: A1.28 (VBAT), U1.23 (VIN)
/VIN_EN: A1.19 (D5), U1.22 (VIN_EN)
/V_Battery: J2.1, J4.3, J5.3, J7.3
/V_PreAmp: J3.4, Q1.3 (E), R4.1, U3.1 (VCC)
/V_PreAmpIn: J2.2, Q1.1 (C), R3.1
/nSHDN: J4.4, J5.4, J7.1
IOVD: A1.2 (3V3), C1.1, R1.1, R2.1, U1.17 (IOVD), U2.7 (VDD)
unnamed: C2.1, Q1.2 (B), R3.2
SCL0: A1.18 (SCL/D21), R1.2, U1.19 (SCL), U2.3 (SCL)
SDA0: A1.17 (SDA/D20), R2.2, U1.20 (SDA), U2.4 (SDA)
VBAT: BT1.1 (+), U2.6 (VBACKUP)
nINT: A1.10 (A5), U2.2 (~INT)

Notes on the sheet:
#define I2S_DOUT 11 #define I2S_BCLK 9 #define I2S_FSYNC (I2S_BCLK+1) // must always be this way

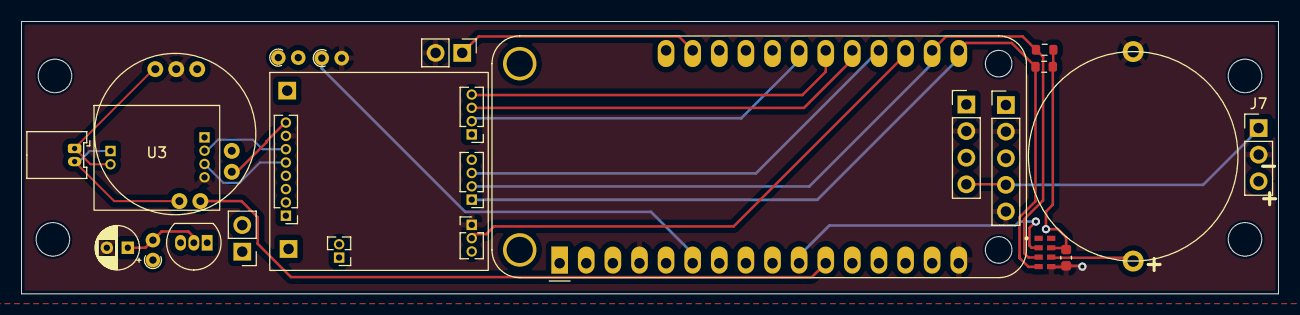
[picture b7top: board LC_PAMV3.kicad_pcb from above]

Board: 4 copper layers, 120.0 x 26.0 mm, 24 parts (0 on the bottom side), 25 nets.
